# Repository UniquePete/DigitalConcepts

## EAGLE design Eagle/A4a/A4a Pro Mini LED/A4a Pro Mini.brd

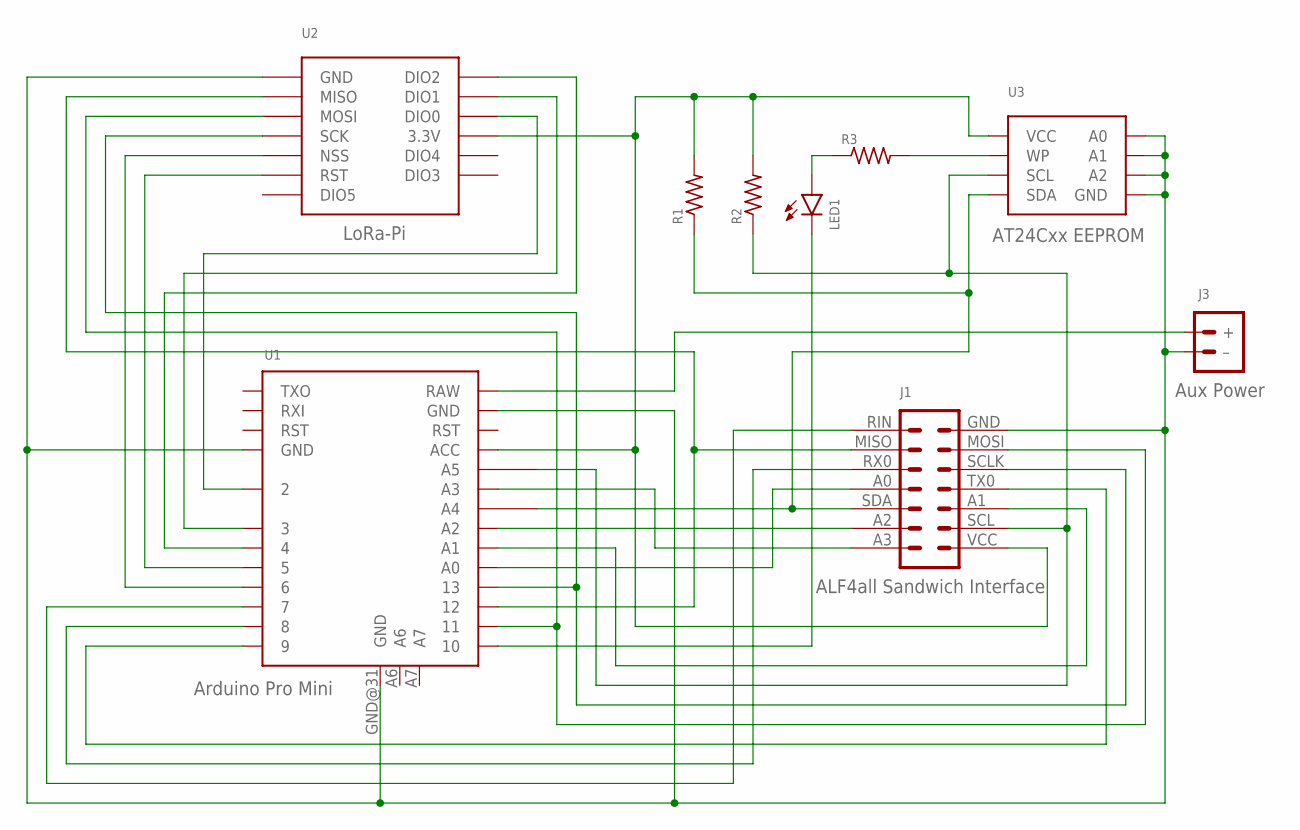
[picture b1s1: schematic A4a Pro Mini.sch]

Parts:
J1: ALF4all Sandwich Interface; CONN_2X7-ALF4ALL-PROCESSOR-B
J3: Aux Power; JST-PH2.0-2-HORIZONTAL
LED1: LEDCHIP-LED0805; CHIP-LED0805
R1, R2, R3: RESISTORR0805; R0805
U1: Arduino Pro Mini; ARDUINO-PRO-MINI-35
U2: LoRa-Pi; RFM95W-PI
U3: AT24Cxx EEPROM; SOP-8

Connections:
GND: J1.GND (7), J3.- (–), U1.GND@11 (GND), U1.GND@22 (GND), U1.GND@31 (GND), U2.GND@3 (GND), U2.GND@6 (GND), U3.P$1 (A0), U3.P$2 (A1), U3.P$3 (A2), U3.P$4 (GND)
unnamed: J1.A0 (11), U1.A0
unnamed: J1.A1 (3), U1.A1
unnamed: J1.A2 (13), U1.A2
unnamed: J1.A3 (14), U1.A3
unnamed: J3.+, U1.RAW
unnamed: J1.SCLK (5), U1.13, U2.SCK
unnamed: J1.RX0 (10), U1.8
unnamed: LED1.C, U1.10
unnamed: J1.RIN (8), U1.7
unnamed: J1.SDA (12), R1.1, U1.A4, U3.P$5 (SDA)
unnamed: J1.SCL (2), R2.1, U1.A5, U3.P$6 (SCL)
unnamed: J1.MISO (9), U1.12, U2.MISO
unnamed: J1.MOSI (6), U1.11, U2.MOSI
unnamed: J1.TX0 (4), U1.9
unnamed: U1.6, U2.NSS
unnamed: U1.5, U2.RST
unnamed: U1.4, U2.DIO2
unnamed: U1.3, U2.DIO1
unnamed: U1.2, U2.DIO0
unnamed: R3.2, U3.P$7 (WP)
unnamed: LED1.A, R3.1
VCC: J1.VCC (1), R1.2, R2.2, U1.ACC, U2.3V3 (3.3V), U3.P$8 (VCC)

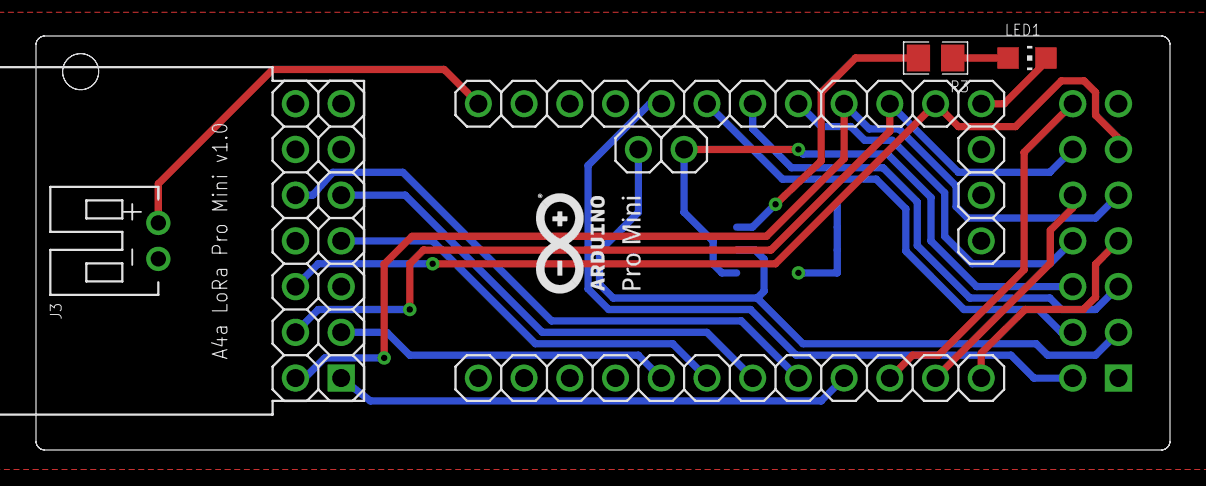
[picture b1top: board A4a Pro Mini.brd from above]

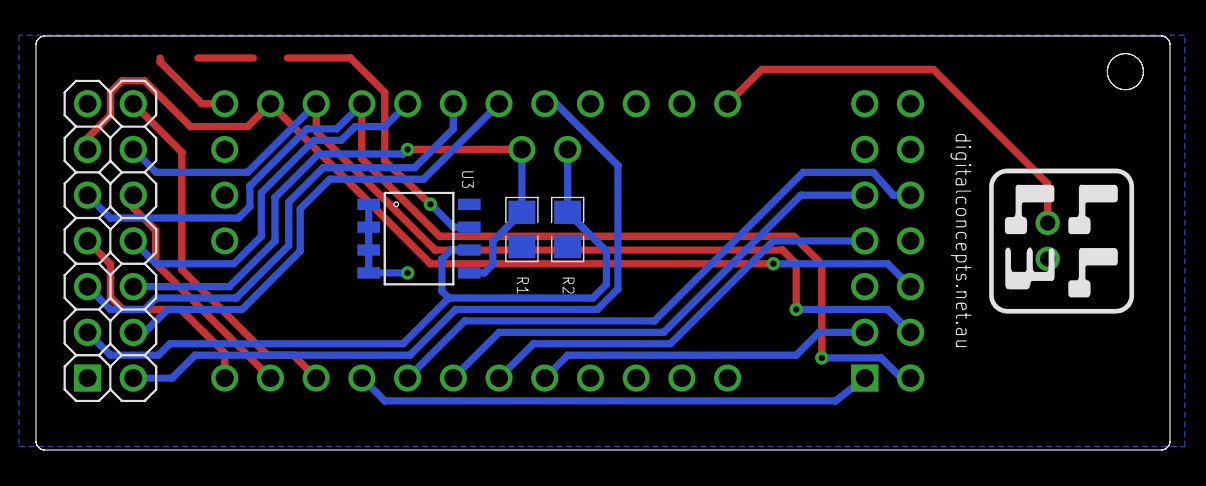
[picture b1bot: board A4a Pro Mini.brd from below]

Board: 2 copper layers, 63.0 x 23.0 mm, 9 parts (3 on the bottom side), 23 nets.

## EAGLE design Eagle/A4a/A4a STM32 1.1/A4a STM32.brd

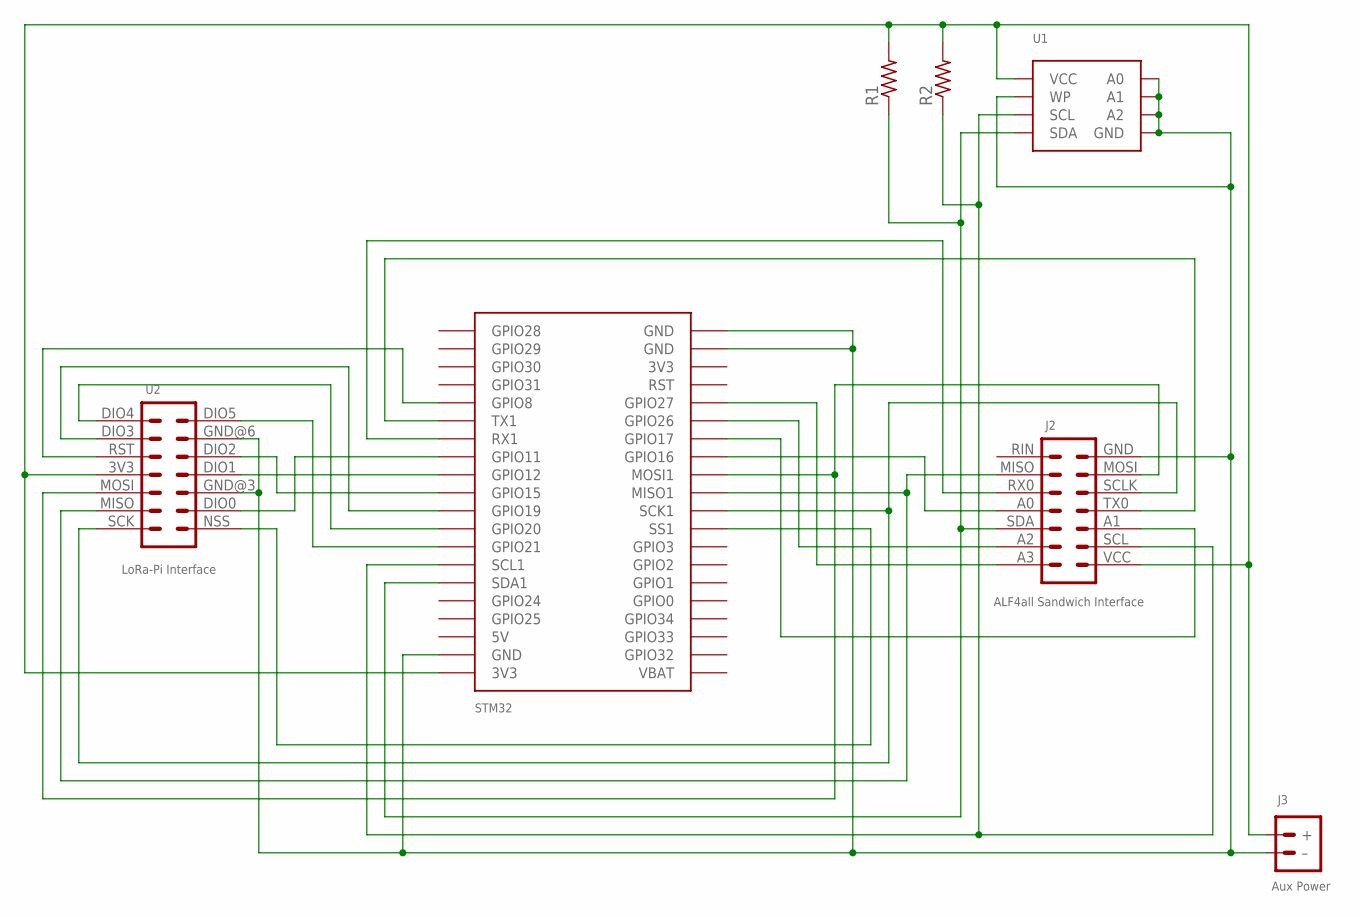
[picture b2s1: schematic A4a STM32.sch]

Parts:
J1: STM32
J2: ALF4all Sandwich Interface; CONN_3X5-ALF4ALL-STM32-INTERCONNECT
J3: Aux Power; JST-PH2.0-2-HORIZONTAL
R1, R2: RESISTORR0805; R0805
U1: AT24CXX-EEPROM-VIA-4; SOP-8-WITH-VIA-4
U2: LoRa-Pi Interface; RFM95W-PI

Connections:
GND: J1.GND@19 (GND), J1.GND@20 (GND), J1.GND@39 (GND), J2.GND (7), J3.- (–), U1.P$1 (A0), U1.P$2 (A1), U1.P$3 (A2), U1.P$4 (GND), U1.P$4@VIA (GND), U1.P$7 (WP), U2.GND@3 (3), U2.GND@6 (6)
unnamed: J1.GPIO10 (RX1), J2.RX0 (10)
unnamed: J1.GPIO26, J2.A2 (13)
unnamed: J1.GPIO22 (SCL1), J2.SCL (2), R2.1, U1.P$6 (SCL)
unnamed: J1.GPIO23 (SDA1), J2.SDA (12), R1.1, U1.P$5 (SDA)
unnamed: J1.GPIO16, J2.A0 (11)
unnamed: J1.GPIO9 (TX1), J2.TX0 (4)
unnamed: J1.GPIO7 (MOSI1), J2.MOSI (6), U2.MOSI (12)
unnamed: J1.GPIO6 (MISO1), J2.MISO (9), U2.MISO (13)
unnamed: J1.GPIO27, J2.A3 (14)
unnamed: J1.GPIO5 (SCK1), J2.SCLK (5), U2.SCK (14)
unnamed: J1.GPIO4 (SS1), U2.NSS (1)
unnamed: J1.GPIO11, U2.DIO0 (2)
unnamed: J1.GPIO12, U2.DIO1 (4)
unnamed: J1.GPIO15, U2.DIO2 (5)
unnamed: J1.GPIO19, U2.DIO3 (9)
unnamed: J1.GPIO20, U2.DIO4 (8)
unnamed: J1.GPIO21, U2.DIO5 (7)
unnamed: J1.GPIO8, U2.RST (10)
unnamed: J1.GPIO17, J2.A1 (3)
VCC: J1.3V3@40 (3V3), J2.VCC (1), J3.+, R1.2, R2.2, U1.P$8 (VCC), U2.3V3 (11)

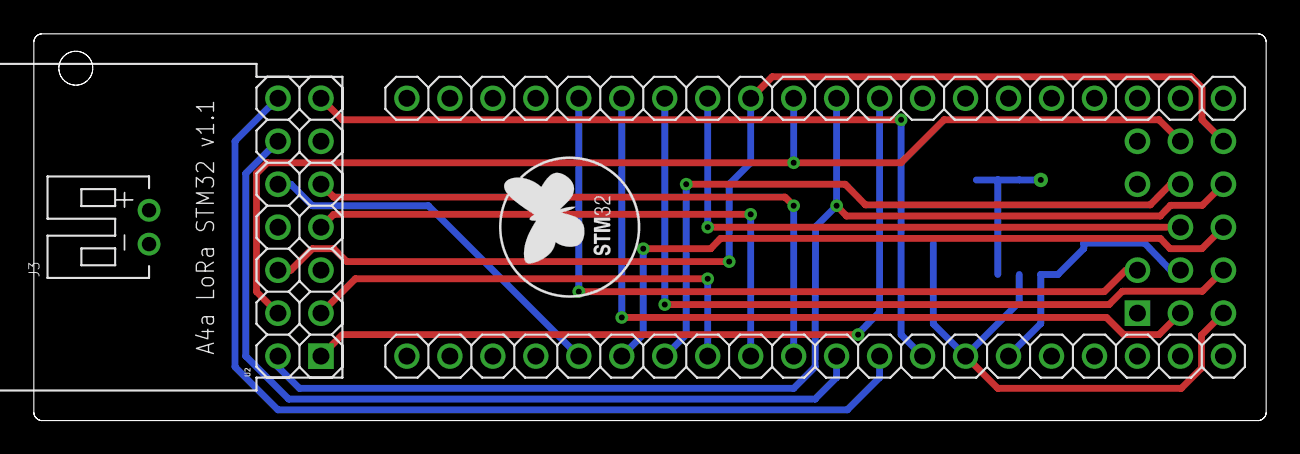
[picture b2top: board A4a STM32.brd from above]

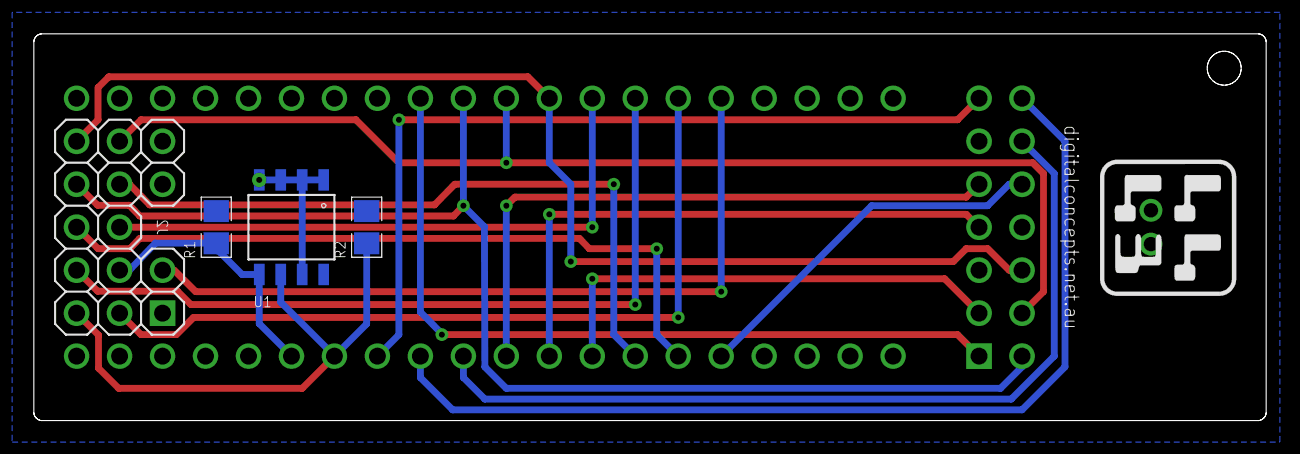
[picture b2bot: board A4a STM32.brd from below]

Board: 2 copper layers, 72.8 x 22.9 mm, 7 parts (3 on the bottom side), 21 nets.

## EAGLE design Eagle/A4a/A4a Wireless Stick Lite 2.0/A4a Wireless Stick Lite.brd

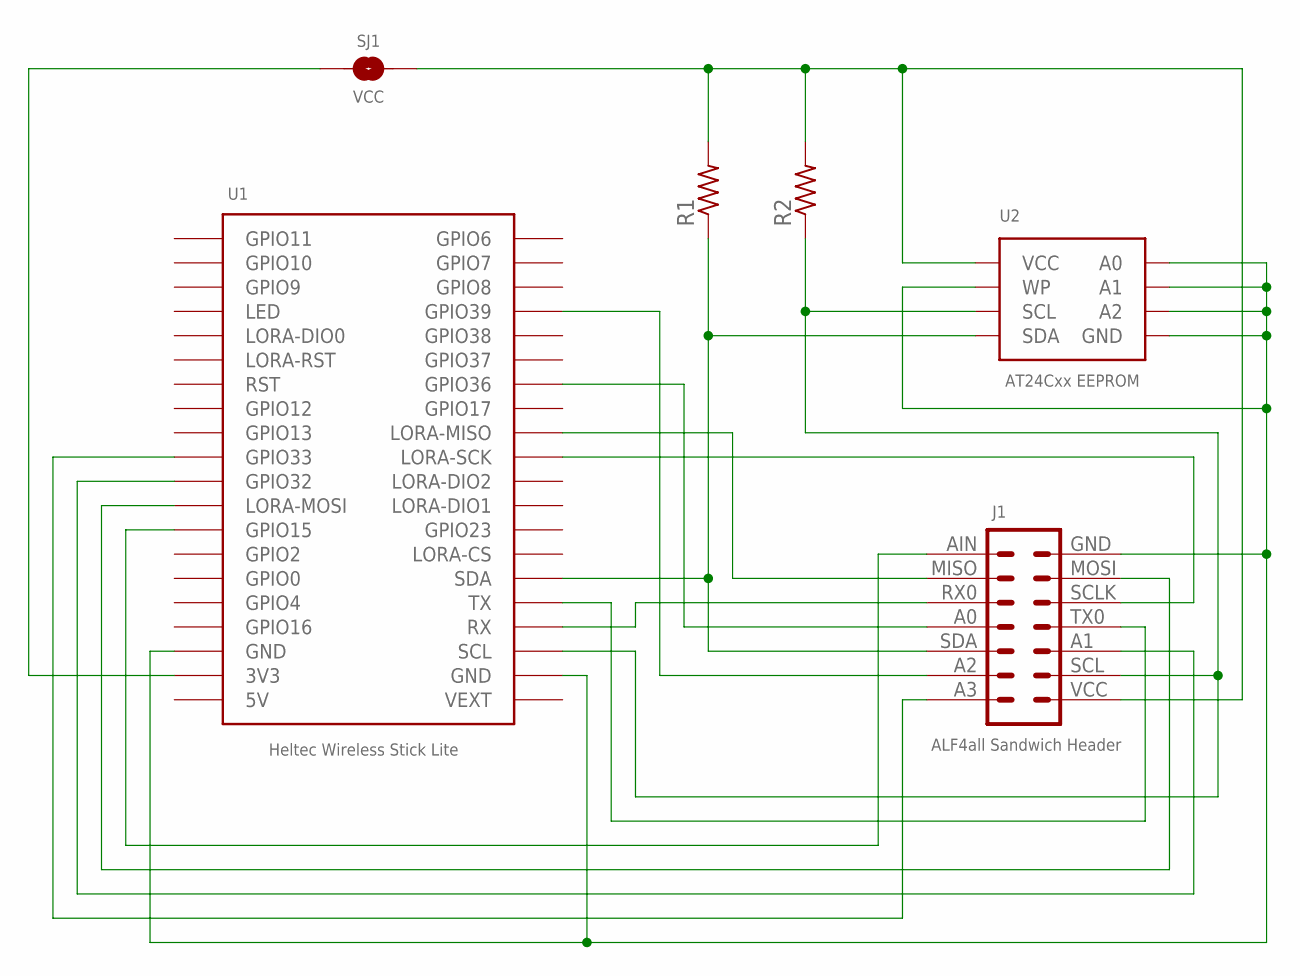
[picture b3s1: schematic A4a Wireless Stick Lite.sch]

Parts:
J1: ALF4all Sandwich Header; CONN_2X7-ALF4ALL-PROCESSOR-B
R1, R2: RESISTOR-VIA-1; R0805-VIA-1
SJ1: VCC; SJ
U1: Heltec Wireless Stick Lite; HELTEC-WIRELESS-STICK-LITE
U2: AT24Cxx EEPROM; SOP-8-WITH-VIA-7

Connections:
GND: J1.GND (7), U1.GND@18 (GND), U1.GND@22 (GND), U2.P$1 (A0), U2.P$2 (A1), U2.P$3 (A2), U2.P$4 (GND), U2.P$7 (WP), U2.P$7@VIA (WP)
unnamed: J1.SCL (2), R2.1, R2.1@VIA (1), U1.SCL, U2.P$6 (SCL)
unnamed: J1.MISO (9), U1.LORA-MISO
unnamed: J1.SCLK (5), U1.LORA-SCK
unnamed: J1.SDA (12), R1.1, R1.1@VIA (1), U1.SDA, U2.P$5 (SDA)
unnamed: J1.RX0 (10), U1.RX
unnamed: J1.TX0 (4), U1.TX
unnamed: J1.A0 (11), U1.GPIO36
unnamed: J1.A2 (13), U1.GPIO39
unnamed: J1.A3 (14), U1.GPIO33
unnamed: J1.MOSI (6), U1.LORA-MOSI
unnamed: J1.A1 (3), U1.GPIO32
unnamed: J1.AIN (8), U1.GPIO15
unnamed: SJ1.1, U1.3V3
VCC: J1.VCC (1), R1.2, R2.2, SJ1.2, U2.P$8 (VCC)

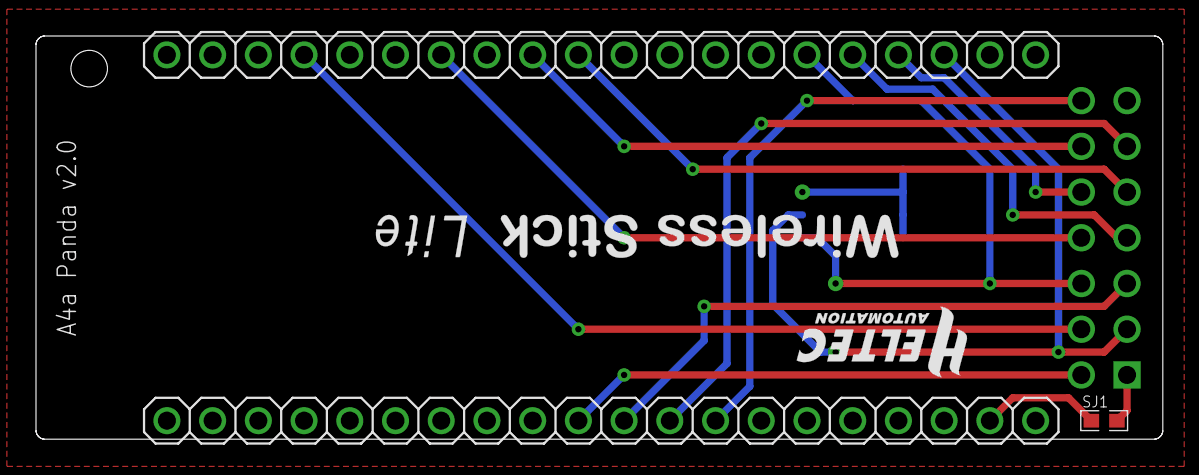
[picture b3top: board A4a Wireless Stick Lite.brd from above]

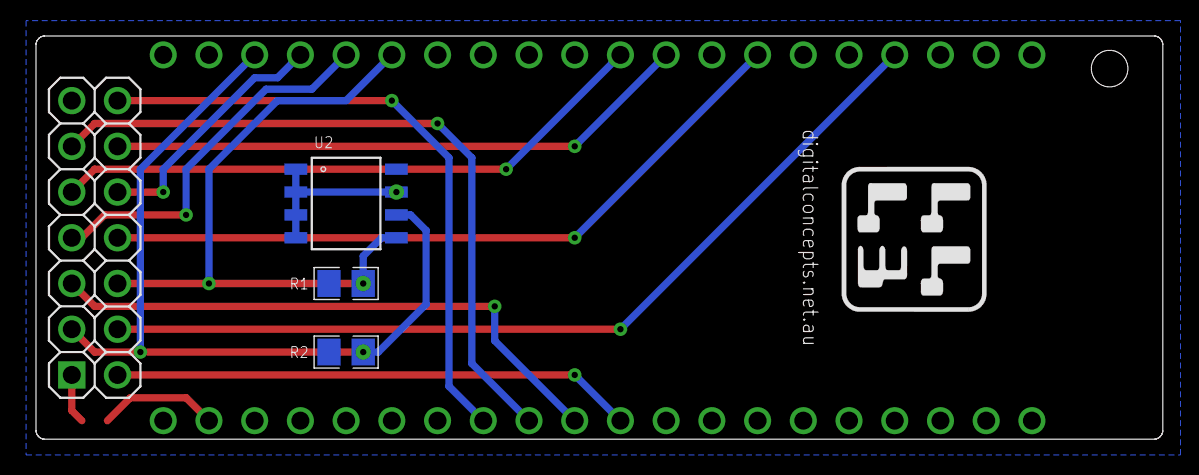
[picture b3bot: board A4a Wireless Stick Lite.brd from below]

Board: 2 copper layers, 62.6 x 22.4 mm, 6 parts (3 on the bottom side), 15 nets.
